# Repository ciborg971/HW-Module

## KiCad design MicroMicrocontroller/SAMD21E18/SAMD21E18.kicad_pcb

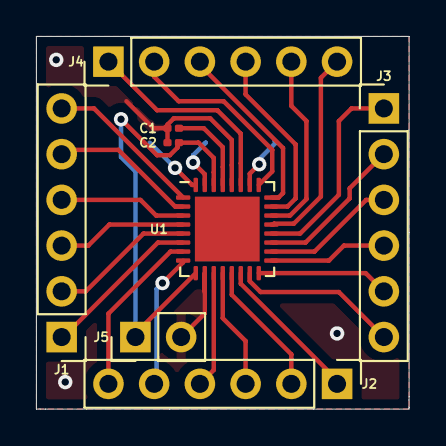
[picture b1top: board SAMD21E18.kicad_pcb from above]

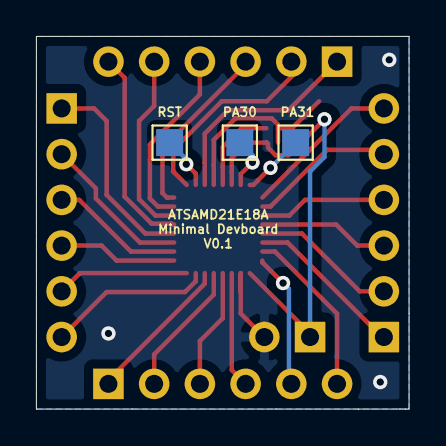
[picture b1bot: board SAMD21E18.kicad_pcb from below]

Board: 2 copper layers, 20.7 x 20.7 mm, 11 parts (3 on the bottom side), 30 nets.

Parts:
C1, C2: 1uF; C_0201_0603Metric
J1, J2, J3, J4: Conn_01x06_Female; PinHeader_1x06_P2.54mm_Vertical
J5: Conn_01x02_Female; PinHeader_1x02_P2.54mm_Vertical
PA30, PA31: TestPoint; TestPoint_Pad_1.5x1.5mm
RST: TestPoint; TestPoint_Pad_1.5x1.5mm
U1: ATSAMD21E18A-M; QFN-32-1EP_5x5mm_P0.5mm_EP3.6x3.6mm

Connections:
+3V3: C2.2, J5.1, U1.9, U1.30
GND: C1.1, C2.1, J5.2, U1.10, U1.28
unnamed: C1.2, U1.29
unnamed: J1.1, U1.6
unnamed: J1.2, U1.5
unnamed: J1.3, U1.4
unnamed: J1.4, U1.3
unnamed: J1.5, U1.2
unnamed: J1.6, U1.1
unnamed: J2.1, U1.14
unnamed: J2.2, U1.13
unnamed: J2.3, U1.12
unnamed: J2.4, U1.11
unnamed: J2.5, U1.8
unnamed: J2.6, U1.7
unnamed: J3.1, U1.20
unnamed: J3.2, U1.19
unnamed: J3.3, U1.18
unnamed: J3.4, U1.17
unnamed: J3.5, U1.16
unnamed: J3.6, U1.15
unnamed: J4.1, U1.27
unnamed: J4.2, U1.25
unnamed: J4.3, U1.24
unnamed: J4.4, U1.23
unnamed: J4.5, U1.22
unnamed: J4.6, U1.21
unnamed: PA30.1, U1.31
unnamed: PA31.1, U1.32
unnamed: RST.1, U1.26

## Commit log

2021-04-18 Full H Bridge with Current Sense V0.1
2021-04-18 ATSAMD21E18A Minimal Devboard V0.1
